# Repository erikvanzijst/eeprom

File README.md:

Parallel EEPROM Programmer
==========================

This is a Shield extension board for Arduino UNO R3 that adds the ability to
read and write parallel EEPROM chips.

This repository contains:

* Arduino code
* Interactive Python based client to read and write to the EEPROM
* KiCad scehmatic and PCB

## Installation and assembly

Install [platformio](https://platformio.org) to compile and upload the firmware
to the Arduino:

    $ platformio run --target upload

Order the PCB either directly from
[Oshpark](https://oshpark.com/shared_projects/gB4fefq3), or use the included
[Gerber files](gerbers/) with any other board house.

With the shield attached to the Uno and hooked up to a computer, fire up the
Python client. To write an image to the EEPROM:

```
$ source ./env/bin/activate
$ cat image.bin | ./eeprom.py load 
Loading 400 bytes into EEPROM...
100%
Complete.
$
```

Full writeup is at https://medium.com/@erikvanzijst/diy-eeprom-programmer-4fd11a486ea

The PCB can be ordered from
[OSH Park](https://oshpark.com/shared_projects/gB4fefq3).

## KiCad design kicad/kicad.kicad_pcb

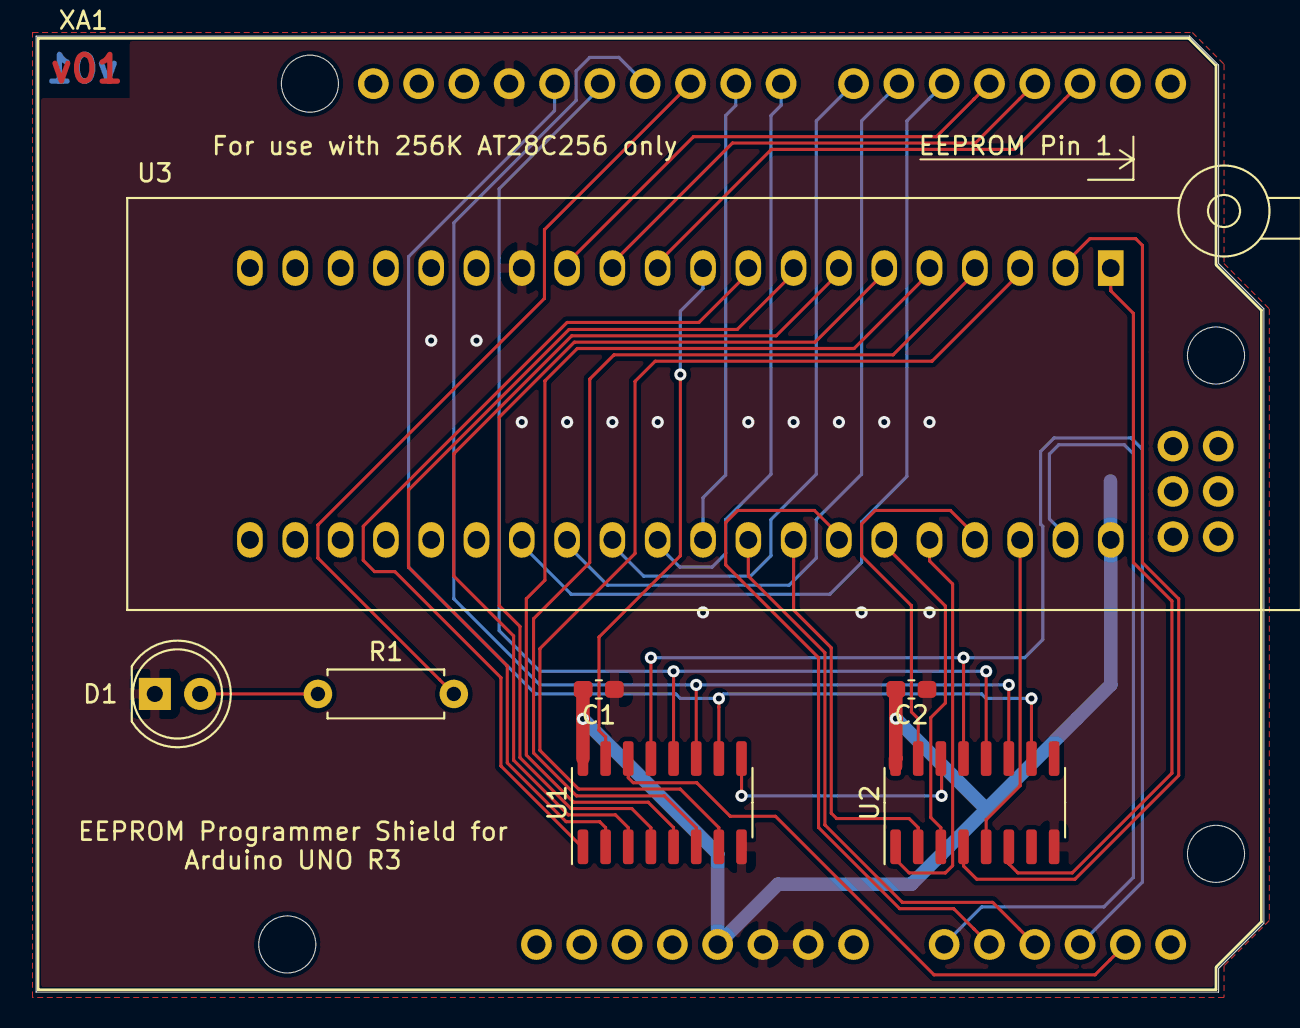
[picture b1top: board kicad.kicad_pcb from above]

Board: 2 copper layers, 68.8 x 53.6 mm, 9 parts (1 on the bottom side), 36 nets.

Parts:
C1, C2, C3: 100nF; C_0603_1608Metric_Pad1.05x0.95mm_HandSolder
D1: Green; LED_D5.0mm
R1: 470R; R_Axial_DIN0207_L6.3mm_D2.5mm_P7.62mm_Horizontal
U1, U2: 74HC595; SOIC-16_3.9x9.9mm_P1.27mm
U3: AT28C256_40PIN_ZIF; DIP_Socket-40_W11.9_W12.7_W15.24_W17.78_W18.5_3M_240-1280-0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
XA1: Arduino_Uno_Shield

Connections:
/IO0: U3.11, XA1.D2
/IO1: U3.12, XA1.D3
/IO2: U3.13, XA1.D4
/IO3: U3.27, XA1.D5
/IO4: U3.28, XA1.D6
/IO5: U3.29, XA1.D7
/IO6: U3.30, XA1.D8
/IO7: U3.31, XA1.D9
/LED: R1.2, XA1.D10
/RCLK: U1.12, U2.12, XA1.D12
/SCLK: U1.11, U2.11, XA1.D11
/SER: U1.14, XA1.A4
/~CE: U3.32, XA1.A2
/~CLR: U1.10, U2.10, XA1.D13
/~OE: U3.34, XA1.A1
/~SOE: U1.13, U2.13, XA1.A3
/~WE: U3.39, XA1.A0
GND: C1.1, C2.1, C3.1, D1.1, U1.8, U2.8, U3.14, XA1.GND1, XA1.GND2, XA1.GND3
unnamed: D1.2, R1.1
unnamed: U1.1, U3.9
unnamed: U1.2, U3.8
unnamed: U1.3, U3.7
unnamed: U1.4, U3.6
unnamed: U1.5, U3.5
unnamed: U1.6, U3.4
unnamed: U1.7, U3.3
unnamed: U1.9, U2.14
unnamed: U1.15, U3.10
unnamed: U2.1, U3.36
unnamed: U2.2, U3.33
unnamed: U2.3, U3.35
unnamed: U2.4, U3.2
unnamed: U2.5, U3.38
unnamed: U2.6, U3.1
unnamed: U2.15, U3.37
VCC: C1.2, C2.2, C3.2, U1.16, U2.16, U3.40, XA1.5V1

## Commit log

2019-05-13 Arduino-Based AT28C256 EEPROM Programmer.
    Initial commit with working reads and full dumps.
2019-05-13 Remove duplicate code.
2019-05-13 Protocol: Fixed length octet for dump command
2019-05-14 Added kicad schematics file.
2019-05-14 Renamed Arduino sketch.
2019-05-14 Added schematic.
2019-05-14 Implemented write command.
2019-05-17 Serial Port Flow Control
    Since the Arduino's serial-over-USB port does not support hardware flow
    control, its tiny 64 byte receive buffer can overflow if data arrives while
    it's tending to other tasks.
    This change puts a cap on the amount of data in flight and defines a
    synchronous, explicit acknowledgement system to implement flow control.
2019-05-20 Flow Control: Added protocol modifications to client.
2019-05-21 Flow Control: Fixed bugs.
2019-08-29 KiCad: Added schematic and PCB for Arduino Shield.
2019-08-29 Added README.
2019-08-29 KiCad: Updated PCB.
2019-08-29 Updated README to link to OSH Park project.
2019-08-29 Added silkscreen logo to PCB.
2019-08-30 KiCad: Added 400dpi logo.
2019-08-30 KiCad: Updated OSH Park permalink and moved cap to backside.
2019-09-01 Added EEPROM chip standby mode for lower power consumption.
2019-09-04 Added EEPROM OE and CLR lines to the Arduino code.
2019-09-04 Added a reset command to interrupt long running operations.
2019-09-04 Added ability to read input straight from stdin, without interactive repl.
2019-09-05 Increased baud rate.
2019-09-05 Added a test command and increased EEPROM write delay to 10ms.
2019-09-06 Added the outlines of an improved test routine.
2019-10-26 Update README.md
    Added link to blog post.
2019-10-26 Changed PCB image in README.
2019-10-26 README: Resized PCB photo.
2019-12-25 Virtualenv: Added a Python virtual env
    This simplifies running the eeprom.py client locally.
2019-12-26 Added Gerber files.
2019-12-26 Converted to PlatformIO
2019-12-26 Added Travis build status badge
2019-12-26 Fixed platformio build command
2019-12-26 Remove old ino project.
2022-08-30 Add protect and unprotect feature
